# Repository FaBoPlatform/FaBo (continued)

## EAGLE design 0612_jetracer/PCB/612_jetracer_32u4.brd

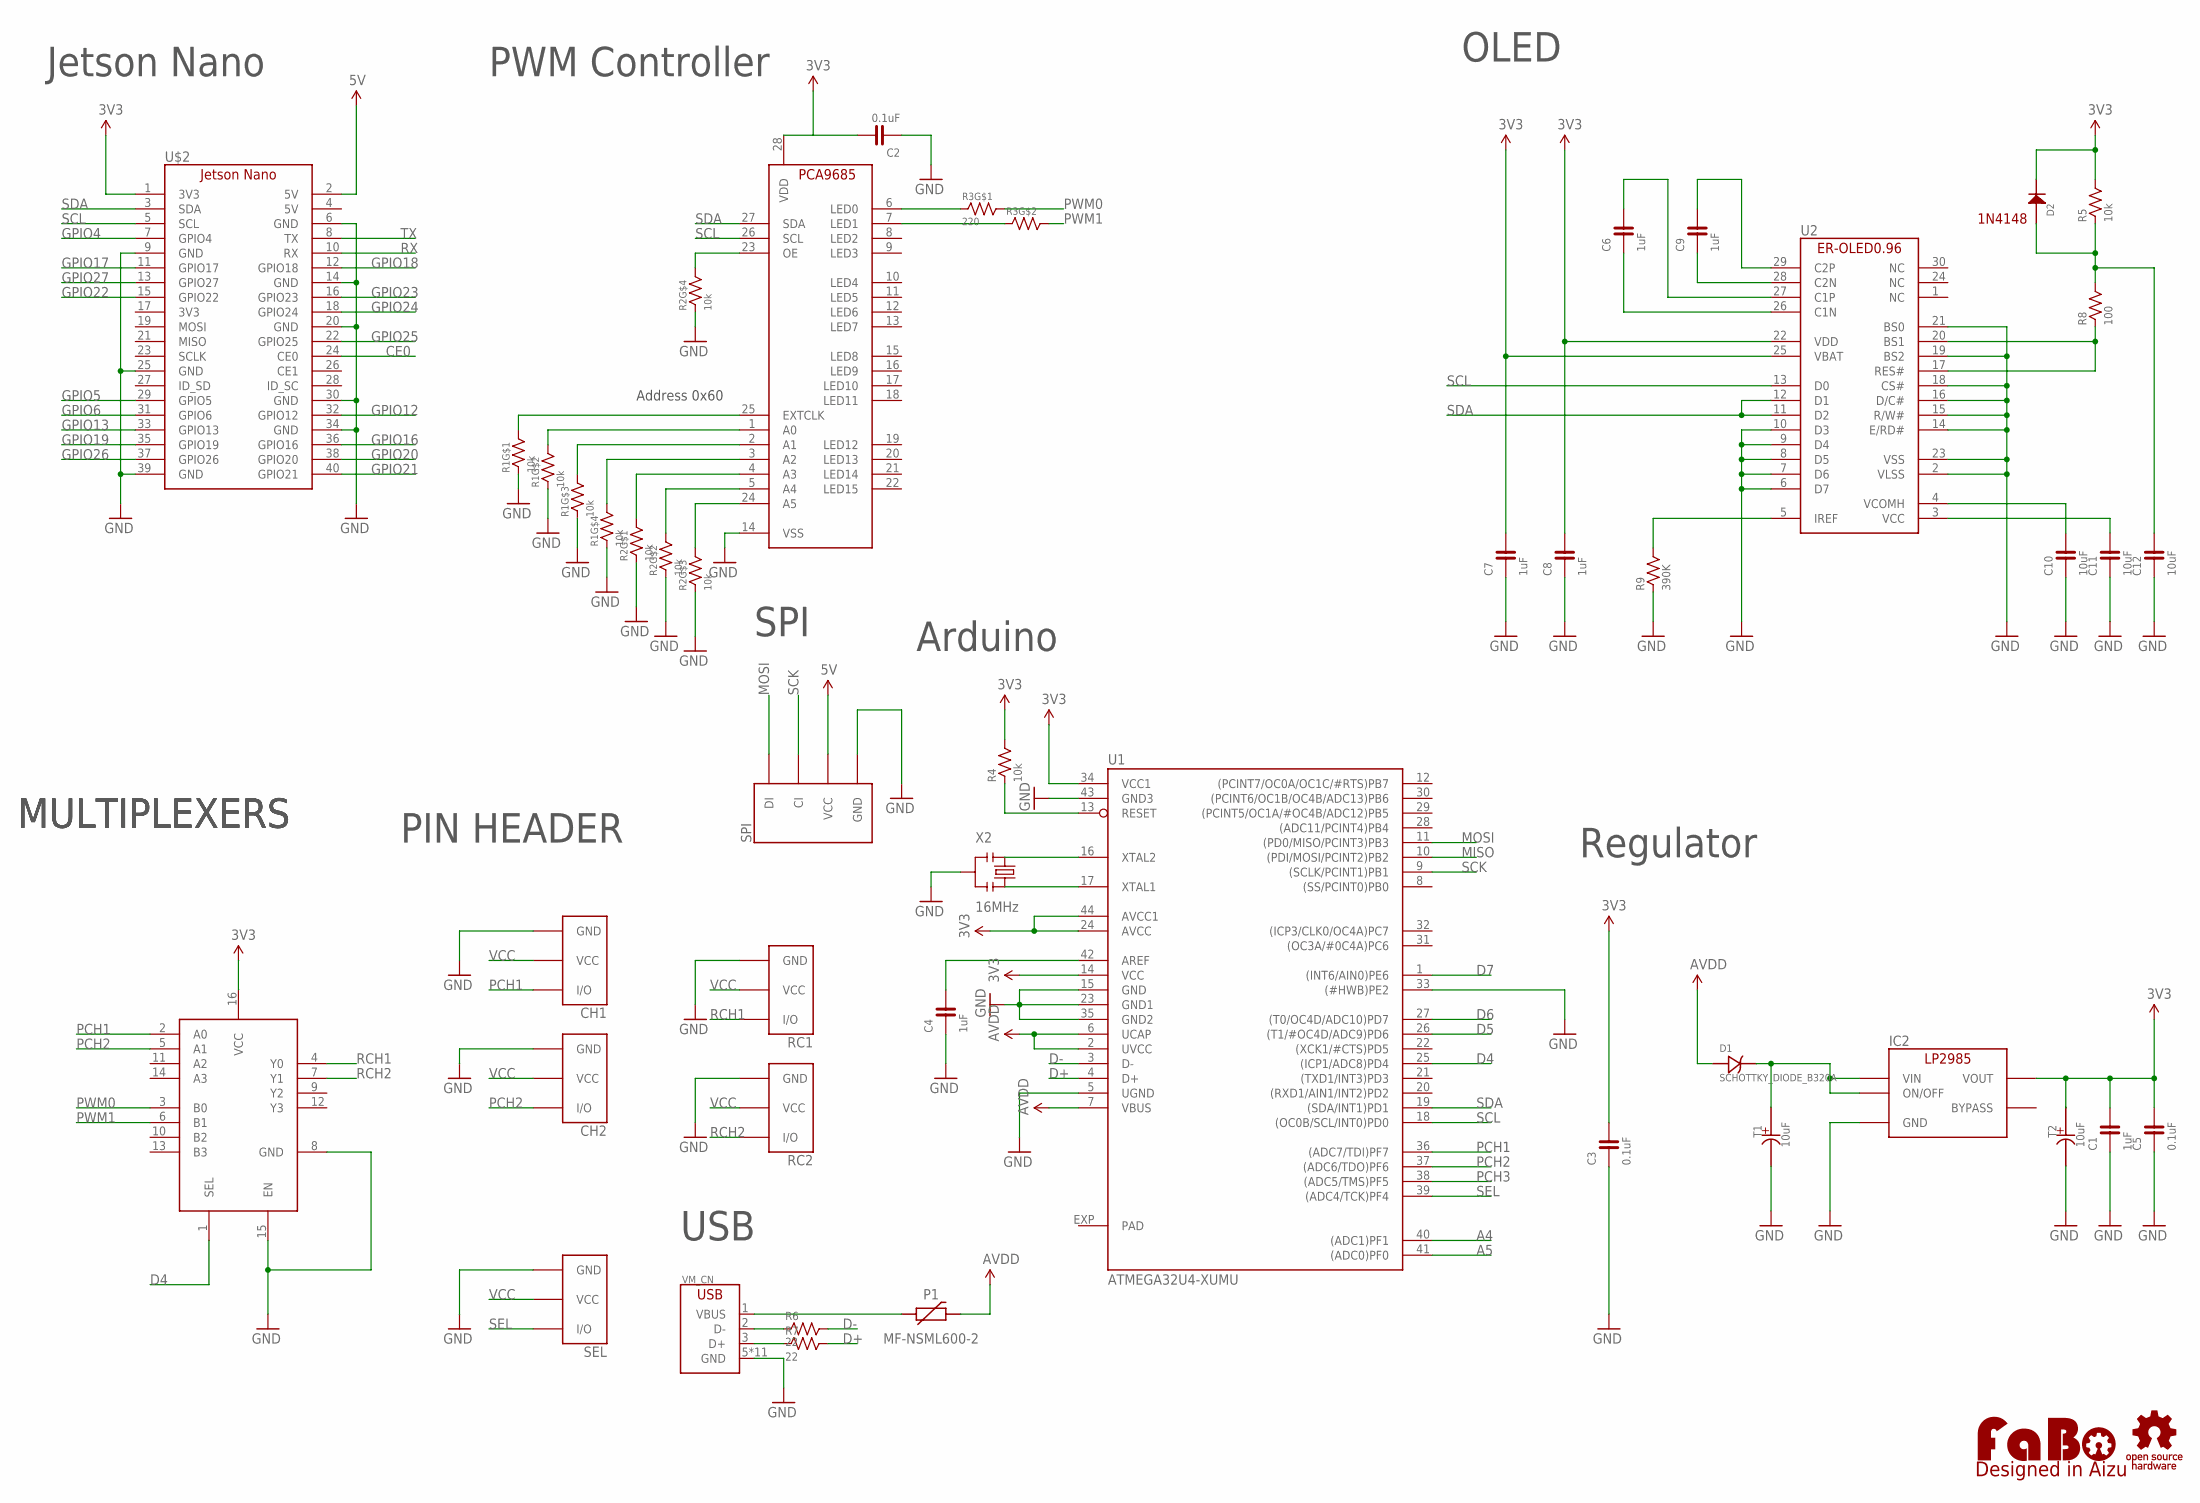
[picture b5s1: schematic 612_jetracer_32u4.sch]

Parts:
C1, C4: 1uF; 0603
C2, C3, C5: 0.1uF; 0603
C6, C7, C8, C9: 1uF; 0603-BOTTOM
C10, C11, C12: 10uF; 0603-BOTTOM
CH1, CH2: FABO_BRICK_3PIN-HEADER; FABO_BRICK_3PIN_HEADER
D1: SCHOTTKY_DIODE_B320A; B320A
D2: 1N4148; 1N4148W
IC2: LP2985-33DBV; SOT-23-5
IC3: MULTIPLEXERSMC74HC157A; TSSOP-16
P1: MF-NSML600-2; 1206
R1, R2: 10k; EXBV8V
R3: 220; EXBV8V
R4: 10k; 0603
R5: 10k; 0603-BOTTOM
R6, R7: 22; 0603
R8: 100; 0603-BOTTOM
R9: 390K; 0603-BOTTOM
RC1, RC2: FABO_BRICK_3PIN-HEADER; FABO_BRICK_3PIN_HEADER
SEL: FABO_BRICK_3PIN-HEADER; FABO_BRICK_3PIN_HEADER
SPI: FABO-SPI-LED-B04B; SPI-B04B-PASK-1
T1, T2: 10uF; 1206-TANTULM
U1: ATMEGA32U4-XUMU; QFN44ML7X7
U2: ER-OLED0.96-1ER-CON30HT-1; ER-CON30HT-1
U$2: JETSON_NANO_NOBORDER; JETSON_NANO_NOBOARDER
U$3: LOGO_OSHW-M_BOTTOM; LOGO_OSHW_M_BOTTOM
U$4: PCA9685_BOTTOM
U$5: LOGO_FABO-M; LOGO_FABO_MS
VM_CN: USB-ZX62D; ZX62D-B-5PA8
X2: 16MHz; CSTNE_V_C

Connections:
3V3: C1.2, C2.2, C3.2, C5.2, C7.2, D2.CATHODE, IC2.5 (VOUT), IC3.16 (VCC), R4.2, R5.2, T2.+, U1.14 (VCC), U1.24 (AVCC), U1.34 (VCC1), U1.44 (AVCC1), U2.25 (VBAT), U$2.1 (3V3), U$4.28 (VDD)
5V: SPI.VCC, U$2.2 (5V)
A4: U1.40 ((ADC1)PF1)
A5: U1.41 ((ADC0)PF0)
AVDD: D1.CATHODE, P1.P$2 (2), U1.2 (UVCC), U1.6 (UCAP), U1.7 (VBUS)
CE0: U$2.24 (CE0)
D4: IC3.1 (SEL), U1.25 ((ICP1/ADC8)PD4)
D5: U1.26 ((T1/#OC4D/ADC9)PD6)
D6: U1.27 ((T0/OC4D/ADC10)PD7)
D7: U1.1 ((INT6/AIN0)PE6)
D+: R7.2, U1.4 (D+)
D-: R6.2, U1.3 (D-)
GND: C1.1, C2.1, C3.1, C4.1, C5.1, C7.1, C8.1, C10.1, C11.1, C12.1, CH1.GND, CH2.GND, IC2.2 (GND), IC3.8 (GND), IC3.15 (EN), R1.1, R1.2 (1), R1.3 (1), R1.4 (1), R2.1, R2.2 (1), R2.3 (1), R2.4 (1), R9.1, RC1.GND, RC2.GND, SEL.GND, SPI.GND, T1.-, T2.-, U1.5 (UGND), U1.15 (GND), U1.23 (GND1), U1.33 ((#HWB)PE2), U1.35 (GND2), U1.43 (GND3), U2.2 (VLSS), U2.6 (D7), U2.7 (D6), U2.8 (D5), U2.9 (D4), U2.10 (D3), U2.14 (E/RD#), U2.15 (R/W#), U2.16 (D/C#), U2.18 (CS#), U2.19 (BS2), U2.21 (BS0), U2.23 (VSS), U$2.6 (GND), U$2.9 (GND), U$2.14 (GND), U$2.20 (GND), U$2.25 (GND), U$2.30 (GND), U$2.34 (GND), U$2.39 (GND), U$4.14 (VSS), VM_CN.5 (GND), VM_CN.B1 (GND), VM_CN.B2 (GND), VM_CN.B3 (GND), VM_CN.B4 (GND), VM_CN.T1 (GND), VM_CN.T2 (GND), VM_CN.T3 (GND), VM_CN.T4 (GND), VM_CN.T5 (GND), VM_CN.T6 (GND), X2.2
GPIO4: U$2.7 (GPIO4)
GPIO5: U$2.29 (GPIO5)
GPIO6: U$2.31 (GPIO6)
GPIO12: U$2.32 (GPIO12)
GPIO13: U$2.33 (GPIO13)
GPIO16: U$2.36 (GPIO16)
GPIO17: U$2.11 (GPIO17)
GPIO18: U$2.12 (GPIO18)
GPIO19: U$2.35 (GPIO19)
GPIO20: U$2.38 (GPIO20)
GPIO21: U$2.40 (GPIO21)
GPIO22: U$2.15 (GPIO22)
GPIO23: U$2.16 (GPIO23)
GPIO24: U$2.18 (GPIO24)
GPIO25: U$2.22 (GPIO25)
GPIO26: U$2.37 (GPIO26)
GPIO27: U$2.13 (GPIO27)
MISO: U1.10 ((PDI/MOSI/PCINT2)PB2)
MOSI: SPI.DI, U1.11 ((PD0/MISO/PCINT3)PB3)
unnamed: R3.1, U$4.6 (LED0)
unnamed: R3.2 (1), U$4.7 (LED1)
unnamed: C4.2, U1.42 (AREF)
unnamed: U1.16 (XTAL2), X2.1
unnamed: R6.1, VM_CN.2 (D-)
unnamed: R2.5 (2), U$4.23 (OE)
unnamed: R1.8 (2), U$4.25 (EXTCLK)
unnamed: R1.7 (2), U$4.1 (A0)
unnamed: R1.6 (2), U$4.2 (A1)
unnamed: R1.5 (2), U$4.3 (A2)
unnamed: R2.8 (2), U$4.4 (A3)
unnamed: R2.7 (2), U$4.5 (A4)
unnamed: U1.17 (XTAL1), X2.3
unnamed: C6.2, U2.27 (C1P)
unnamed: R4.1, U1.13 (RESET)
unnamed: R7.1, VM_CN.3 (D+)
unnamed: D1.ANODE, IC2.1 (VIN), IC2.3 (ON/OFF), T1.+
unnamed: R2.6 (2), U$4.24 (A5)
unnamed: C6.1, U2.26 (C1N)
unnamed: C9.1, U2.28 (C2N)
unnamed: C9.2, U2.29 (C2P)
unnamed: R9.2, U2.5 (IREF)
unnamed: C10.2, U2.4 (VCOMH)
unnamed: C11.2, U2.3 (VCC)
unnamed: R8.1, U2.17 (RES#), U2.20 (BS1)
unnamed: C12.2, D2.ANODE, R5.1, R8.2
unnamed: C8.2, U2.22 (VDD)
PAD: U1.EXP (PAD)
PCH1: CH1.I/O, IC3.2 (A0), U1.36 ((ADC7/TDI)PF7)
PCH2: CH2.I/O, IC3.5 (A1), U1.37 ((ADC6/TDO)PF6)
PCH3: U1.38 ((ADC5/TMS)PF5)
PTCP1: P1.P$1 (1), VM_CN.1 (VBUS)
PWM0: IC3.3 (B0), R3.8 (2)
PWM1: IC3.6 (B1), R3.7 (2)
RCH1: IC3.4 (Y0), RC1.I/O
RCH2: IC3.7 (Y1), RC2.I/O
RX: U$2.10 (RX)
SCK: SPI.CI, U1.9 ((SCLK/PCINT1)PB1)
SCL: U1.18 ((OC0B/SCL/INT0)PD0), U2.13 (D0), U$2.5 (SCL), U$4.26 (SCL)
SDA: U1.19 ((SDA/INT1)PD1), U2.11 (D2), U2.12 (D1), U$2.3 (SDA), U$4.27 (SDA)
SEL: SEL.I/O, U1.39 ((ADC4/TCK)PF4)
TX: U$2.8 (TX)
VCC: CH1.VCC, CH2.VCC, RC1.VCC, RC2.VCC, SEL.VCC

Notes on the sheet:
Jetson Nano
PWM Controller
MULTIPLEXERS
Address 0x60
PIN HEADER
Regulator
SPI
USB
Arduino
1N4148
OLED

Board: 2 copper layers, 42 parts (0 on the bottom side), 47 nets, no tracks yet.

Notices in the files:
parts and their libraries:
FaBo-Resistors: Released under the Creative Commons Attribution-ShareAlike 4.0 License
https://creativecommons.org/licenses/by-sa/4.0
FaBo-etc: Released under the Creative Commons
